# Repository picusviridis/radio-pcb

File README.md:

# radio-pcb
PCB Designs for Radio Components

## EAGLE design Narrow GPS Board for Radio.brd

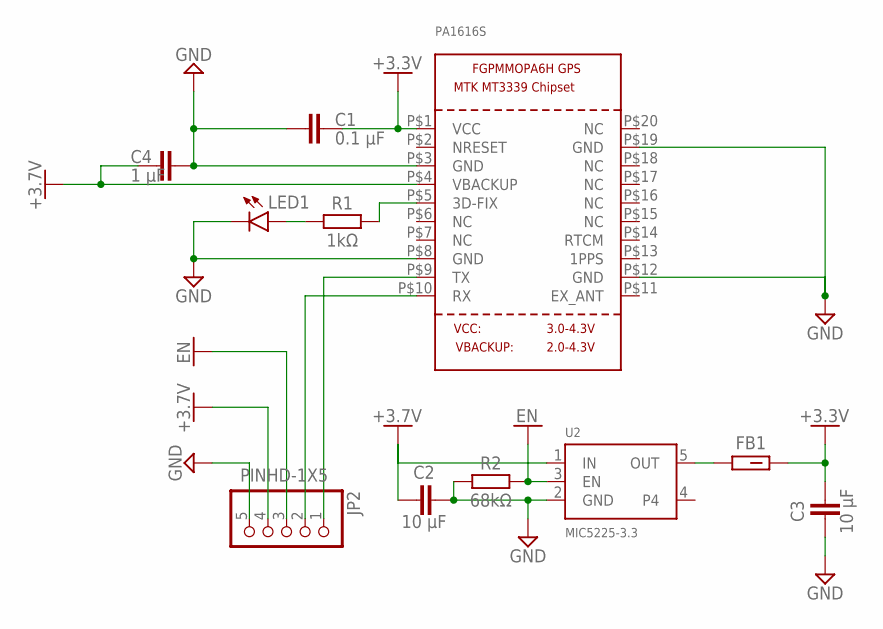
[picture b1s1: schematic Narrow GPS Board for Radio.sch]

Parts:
C1: 0.1 µF; 0805
C2, C3: 10 µF; 0805
C4: 1 µF; 0805
FB1: 600 Ohms @ 100 MHz; BEADC2012X105N
JP2: PINHD-1X5; 1X05
LED1: LED_RED; LEDC2012X110N_FLAT-R
PA1616S: GPS_FGPMMOPA6H; FGPMMOPA6H
R1: 1kΩ; RESC2012X65
R2: 68kΩ; RESC2012X65
U2: MIC5225-3.3; SOT23-5

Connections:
+3.3V: C1.1, C3.2, FB1.2, PA1616S.P$1 (VCC)
+3.7V: C2.1, C4.2, JP2.4, PA1616S.P$4 (VBACKUP), U2.1 (IN)
EN: JP2.3, R2.2, U2.3 (EN)
FIX: PA1616S.P$5 (3D-FIX), R1.2
GND: C1.2, C2.2, C3.1, C4.1, JP2.5, LED1.C, PA1616S.P$3 (GND), PA1616S.P$8 (GND), PA1616S.P$12 (GND), PA1616S.P$19 (GND), R2.1, U2.2 (GND)
unnamed: LED1.A, R1.1
OUT: FB1.1, U2.5 (OUT)
RX: JP2.2, PA1616S.P$10 (RX)
TX: JP2.1, PA1616S.P$9 (TX)

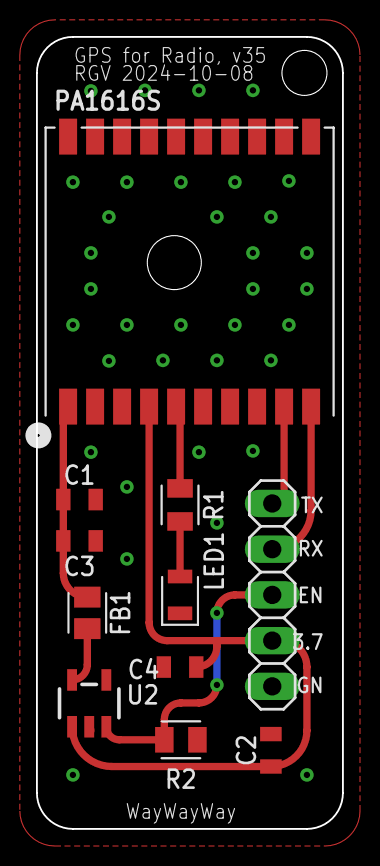
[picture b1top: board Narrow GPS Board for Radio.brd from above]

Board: 2 copper layers, 17.0 x 44.0 mm, 11 parts (0 on the bottom side), 9 nets.

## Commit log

2024-10-26 Create LICENSE
2024-10-26 Added schematic and PCB board design for GPS
2024-10-26 Rename Screenshot 2024-10-26 001431.png to attachments/gps_board_rendering.png

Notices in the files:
parts and their libraries:
SparkFun-Capacitors: Licensing: Creative Commons ShareAlike 4.0 International - https://creativecommons.org/licenses/by-sa/4.0
